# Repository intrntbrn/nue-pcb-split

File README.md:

# nue-pcb-split

- removed ansi bottom row (6.25u)
- removed iso support (split leftshift and iso enter)
- added 10u stabilizer holes
- added 1-2.75-2.25-1 split space option
- not tested! please select "confirm parts placement" when ordering from jlcpcb
  (this is due to jst connector shortage).

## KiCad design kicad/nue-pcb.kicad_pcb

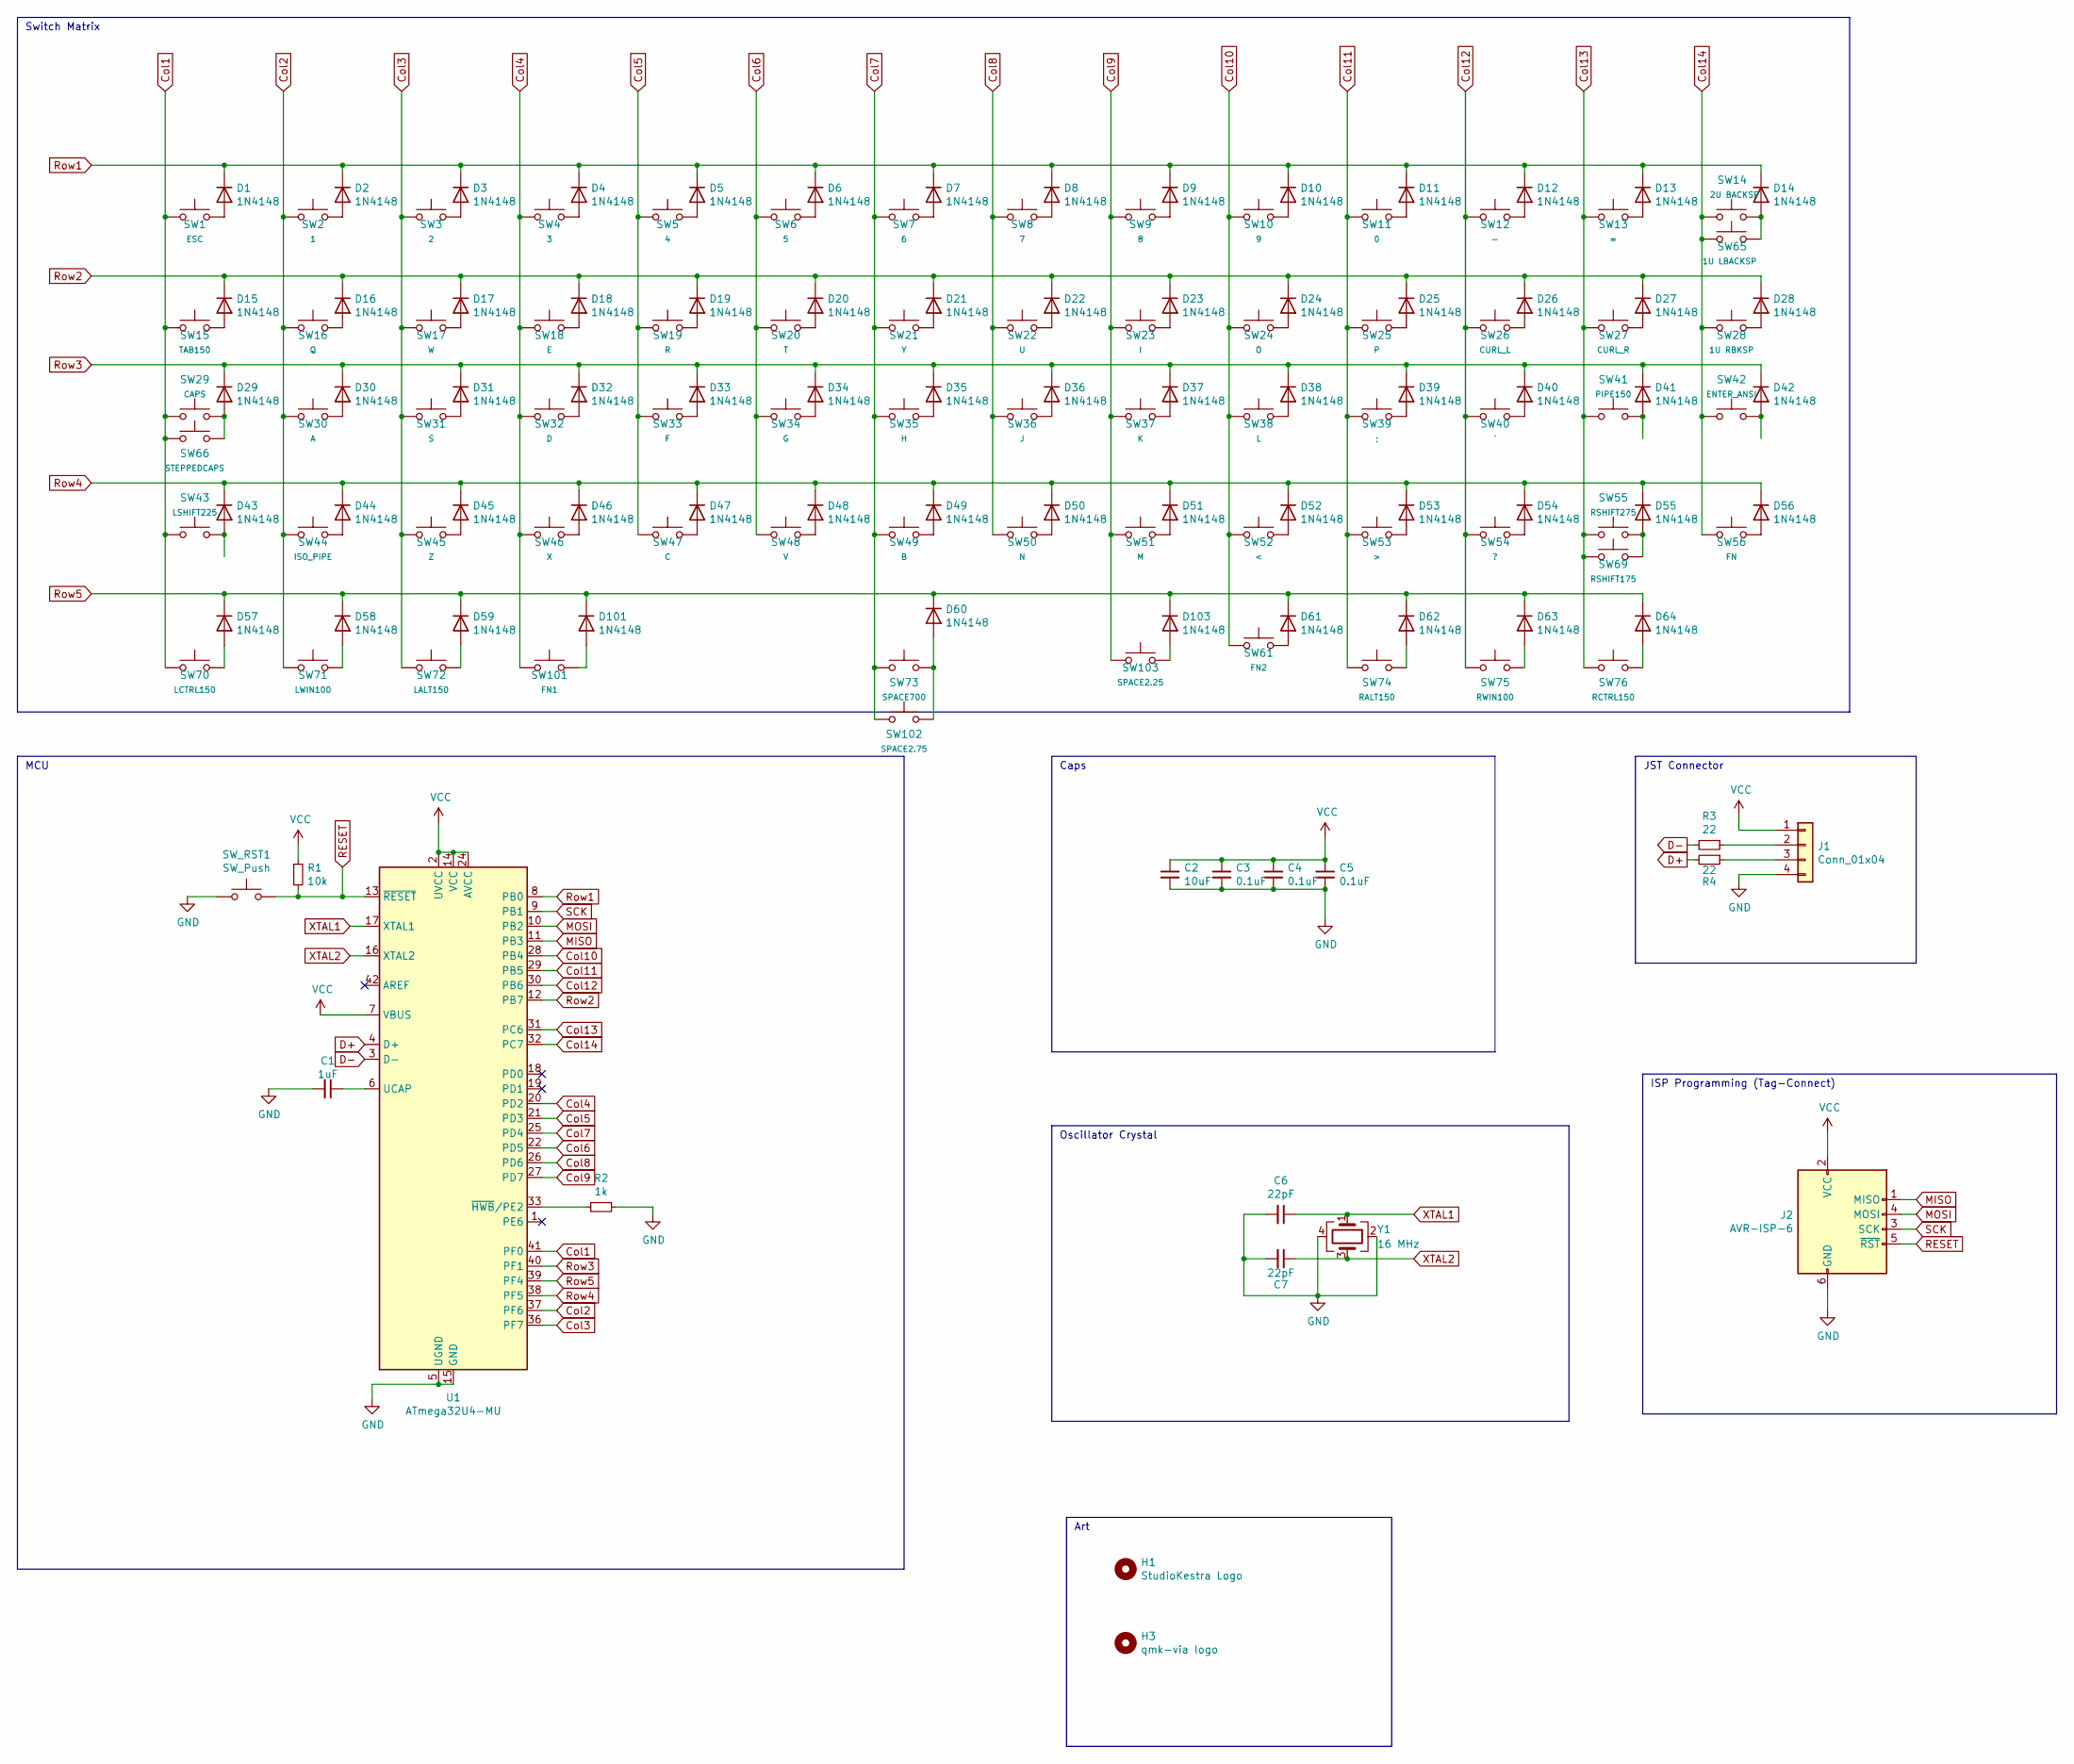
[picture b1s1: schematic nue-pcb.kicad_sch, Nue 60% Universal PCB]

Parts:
C1: 1uF; C_0603_1608Metric
C2: 10uF; C_0603_1608Metric
C3, C4, C5: 0.1uF; C_0603_1608Metric
C6, C7: 22pF; C_0603_1608Metric
D1, D2, D3, D4, D5, D6, D7, D8, D9, D10, D11, D12, D13, D14, D15, D16, D17, D18, D19, D20, D21, D22, D23, D24, D25, D26, D27, D28, D29, D30, D31, D32, D33, D34, D35, D36, D37, D38, D39, D40, D41, D42, D43, D44, D45, D46, D47, D48, D49, D50, D51, D52, D53, D54, D55, D56, D57, D58, D59, D60, D61, D62, D63, D64, D101, D103: 1N4148; D_SOD-123
H1: StudioKestra Logo; sk-square-mask-md
H3: qmk-via logo; qmk-via
J1: Conn_01x04; JST_BM04B-ASRS
J2: AVR-ISP-6; Conn_AVR_ISP_6
R1: 10k; R_0603_1608Metric
R2: 1k; R_0603_1608Metric
R3, R4: 22; R_0603_1608Metric
SW1: ESC; MX100
SW2: 1; MX100
SW3: 2; MX100
SW4: 3; MX100
SW5: 4; MX100
SW6: 5; MX100
SW7: 6; MX100
SW8: 7; MX100
SW9: 8; MX100
SW10: 9; MX100
SW11: 0; MX100
SW12: -; MX100
SW13: =; MX100
SW14: 2U BACKSP; MX200
SW15: TAB150; MX150
SW16: Q; MX100
SW17: W; MX100
SW18: E; MX100
SW19: R; MX100
SW20: T; MX100
SW21: Y; MX100
SW22: U; MX100
SW23: I; MX100
SW24: O; MX100
SW25: P; MX100
SW26: CURL_L; MX100
SW27: CURL_R; MX100
SW28: 1U RBKSP; MX100
SW29: CAPS; MX175
SW30: A; MX100
SW31: S; MX100
SW32: D; MX100
SW33: F; MX100
SW34: G; MX100
SW35: H; MX100
SW36: J; MX100
SW37: K; MX100
SW38: L; MX100
SW39: ;; MX100
SW40: '; MX100
SW41: PIPE150; MX150
SW42: ENTER_ANSI; MX225R
SW43: LSHIFT225; MX225
SW44: ISO_PIPE; MX100
SW45: Z; MX100
SW46: X; MX100
SW47: C; MX100
SW48: V; MX100
SW49: B; MX100
SW50: N; MX100
SW51: M; MX100
SW52: <; MX100
SW53: >; MX100
SW54: ?; MX100
SW55: RSHIFT275; MX275
SW56: FN; MX100
SW61: FN2; MX100
SW65: 1U LBACKSP; MX100
SW66: STEPPEDCAPS; MX125
SW69: RSHIFT175; MX175
SW70: LCTRL150; MX150
SW71: LWIN100; MX100
SW72: LALT150; MX150
SW73: SPACE700; MX10-7U
SW74: RALT150; MX150
SW75: RWIN100; MX100
SW76: RCTRL150; MX150
SW101: FN1; MX100
SW102: SPACE2.75; MX275R
SW103: SPACE2.25; MX225R
SW_RST1: SW_Push; pushbtn_C319436
U1: ATmega32U4-MU; QFN-44-1EP_7x7mm_P0.5mm_EP5.2x5.2mm
Y1: 16 MHz; Crystal_SMD_2520-4Pin_2.5x2.0mm

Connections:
Col1: SW1.1, SW15.1, SW29.1, SW43.1, SW66.1, SW70.1, U1.41 (PF0)
Col2: SW2.1, SW16.1, SW30.1, SW44.1, SW71.1, U1.37 (PF6)
Col3: SW3.1, SW17.1, SW31.1, SW45.1, SW72.1, U1.36 (PF7)
Col4: SW4.1, SW18.1, SW32.1, SW46.1, SW101.1, U1.20 (PD2)
Col5: SW5.1, SW19.1, SW33.1, SW47.1, U1.21 (PD3)
Col6: SW6.1, SW20.1, SW34.1, SW48.1, U1.22 (PD5)
Col7: SW7.1, SW21.1, SW35.1, SW49.1, SW73.2, SW102.2, U1.25 (PD4)
Col8: SW8.1, SW22.1, SW36.1, SW50.1, U1.26 (PD6)
Col9: SW9.1, SW23.1, SW37.1, SW51.1, SW103.1, U1.27 (PD7)
Col10: SW10.1, SW24.1, SW38.1, SW52.1, SW61.1, U1.28 (PB4)
Col11: SW11.1, SW25.1, SW39.1, SW53.1, SW74.1, U1.29 (PB5)
Col12: SW12.1, SW26.1, SW40.1, SW54.1, SW75.1, U1.30 (PB6)
Col13: SW13.1, SW27.1, SW41.1, SW55.1, SW69.1, SW76.1, U1.31 (PC6)
Col14: SW14.1, SW28.1, SW42.1, SW56.1, SW65.1, U1.32 (PC7)
D+: R4.2, U1.4 (D+)
D-: R3.2, U1.3 (D-)
GND: C1.2, C2.2, C3.2, C4.2, C5.2, C6.2, C7.2, J1.4, J2.6 (GND), R2.1, SW_RST1.1, U1.5 (UGND), U1.15 (GND), U1.23 (GND), U1.35 (GND), U1.43 (GND), U1.45 (GND), Y1.2, Y1.4
MISO: J2.1 (MISO), U1.11 (PB3)
MOSI: J2.4 (MOSI), U1.10 (PB2)
unnamed: C1.1, U1.6 (UCAP)
unnamed: D1.2 (A), SW1.2
unnamed: D2.2 (A), SW2.2
unnamed: D3.2 (A), SW3.2
unnamed: D4.2 (A), SW4.2
unnamed: D5.2 (A), SW5.2
unnamed: D6.2 (A), SW6.2
unnamed: D7.2 (A), SW7.2
unnamed: D8.2 (A), SW8.2
unnamed: D9.2 (A), SW9.2
unnamed: D10.2 (A), SW10.2
unnamed: D11.2 (A), SW11.2
unnamed: D12.2 (A), SW12.2
unnamed: D13.2 (A), SW13.2
unnamed: D14.2 (A), SW14.2, SW65.2
unnamed: D15.2 (A), SW15.2
unnamed: D16.2 (A), SW16.2
unnamed: D17.2 (A), SW17.2
unnamed: D18.2 (A), SW18.2
unnamed: D19.2 (A), SW19.2
unnamed: D20.2 (A), SW20.2
unnamed: D21.2 (A), SW21.2
unnamed: D22.2 (A), SW22.2
unnamed: D23.2 (A), SW23.2
unnamed: D24.2 (A), SW24.2
unnamed: D25.2 (A), SW25.2
unnamed: D26.2 (A), SW26.2
unnamed: D27.2 (A), SW27.2
unnamed: D28.2 (A), SW28.2
unnamed: D29.2 (A), SW29.2, SW66.2
unnamed: D30.2 (A), SW30.2
unnamed: D31.2 (A), SW31.2
unnamed: D32.2 (A), SW32.2
unnamed: D33.2 (A), SW33.2
unnamed: D34.2 (A), SW34.2
unnamed: D35.2 (A), SW35.2
unnamed: D36.2 (A), SW36.2
unnamed: D37.2 (A), SW37.2
unnamed: D38.2 (A), SW38.2
unnamed: D39.2 (A), SW39.2
unnamed: D40.2 (A), SW40.2
unnamed: D41.2 (A), SW41.2
unnamed: D42.2 (A), SW42.2
unnamed: D43.2 (A), SW43.2
unnamed: D44.2 (A), SW44.2
unnamed: D45.2 (A), SW45.2
unnamed: D46.2 (A), SW46.2
unnamed: D47.2 (A), SW47.2
unnamed: D48.2 (A), SW48.2
unnamed: D49.2 (A), SW49.2
unnamed: D50.2 (A), SW50.2
unnamed: D51.2 (A), SW51.2
unnamed: D52.2 (A), SW52.2
unnamed: D53.2 (A), SW53.2
unnamed: D54.2 (A), SW54.2
unnamed: D55.2 (A), SW55.2, SW69.2
unnamed: D56.2 (A), SW56.2
unnamed: D57.2 (A), SW70.2
unnamed: D58.2 (A), SW71.2
unnamed: D59.2 (A), SW72.2
unnamed: D60.2 (A), SW73.1, SW102.1
unnamed: D61.2 (A), SW61.2
unnamed: D62.2 (A), SW74.2
unnamed: D63.2 (A), SW75.2
unnamed: D64.2 (A), SW76.2
unnamed: D101.2 (A), SW101.2
unnamed: D103.2 (A), SW103.2
unnamed: J1.2, R3.1
unnamed: J1.3, R4.1
unnamed: R2.2, U1.33 (~HWB/PE2)
RESET: J2.5 (~RST), R1.2, SW_RST1.2, U1.13 (~RESET)
Row1: D1.1 (K), D2.1 (K), D3.1 (K), D4.1 (K), D5.1 (K), D6.1 (K), D7.1 (K), D8.1 (K), D9.1 (K), D10.1 (K), D11.1 (K), D12.1 (K), D13.1 (K), D14.1 (K), U1.8 (PB0)
Row2: D15.1 (K), D16.1 (K), D17.1 (K), D18.1 (K), D19.1 (K), D20.1 (K), D21.1 (K), D22.1 (K), D23.1 (K), D24.1 (K), D25.1 (K), D26.1 (K), D27.1 (K), D28.1 (K), U1.12 (PB7)
Row3: D29.1 (K), D30.1 (K), D31.1 (K), D32.1 (K), D33.1 (K), D34.1 (K), D35.1 (K), D36.1 (K), D37.1 (K), D38.1 (K), D39.1 (K), D40.1 (K), D41.1 (K), D42.1 (K), U1.40 (PF1)
Row4: D43.1 (K), D44.1 (K), D45.1 (K), D46.1 (K), D47.1 (K), D48.1 (K), D49.1 (K), D50.1 (K), D51.1 (K), D52.1 (K), D53.1 (K), D54.1 (K), D55.1 (K), D56.1 (K), U1.38 (PF5)
Row5: D57.1 (K), D58.1 (K), D59.1 (K), D60.1 (K), D61.1 (K), D62.1 (K), D63.1 (K), D64.1 (K), D101.1 (K), D103.1 (K), U1.39 (PF4)
SCK: J2.3 (SCK), U1.9 (PB1)
VCC: C2.1, C3.1, C4.1, C5.1, J1.1, J2.2 (VCC), R1.1, U1.2 (UVCC), U1.7 (VBUS), U1.14 (VCC), U1.24 (AVCC), U1.34 (VCC), U1.44 (AVCC)
XTAL1: C6.1, U1.17 (XTAL1), Y1.1
XTAL2: C7.1, U1.16 (XTAL2), Y1.3

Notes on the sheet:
Oscillator Crystal
MCU
ISP Programming (Tag-Connect)
JST Connector
Caps
Switch Matrix
Art

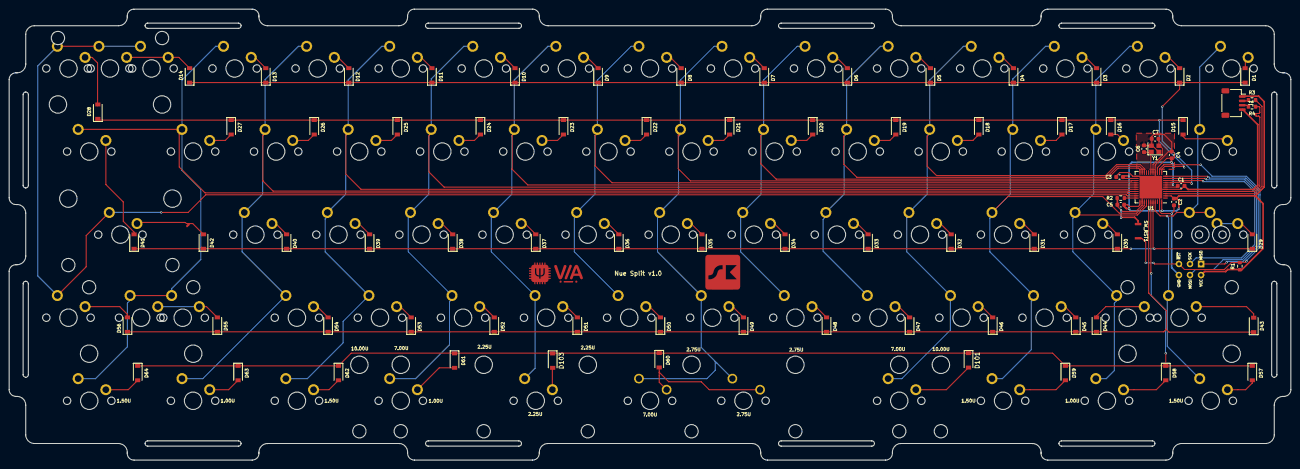
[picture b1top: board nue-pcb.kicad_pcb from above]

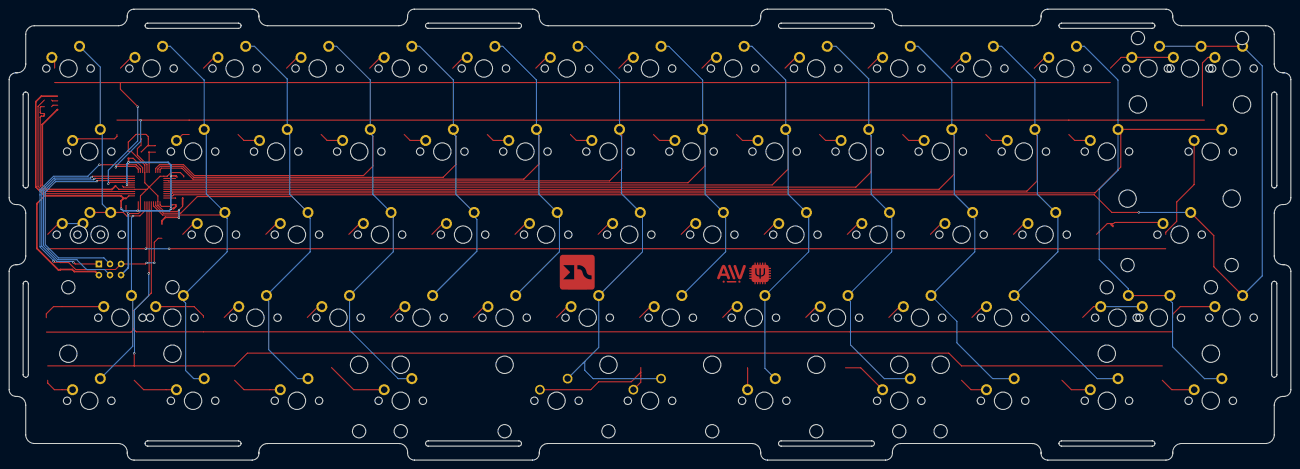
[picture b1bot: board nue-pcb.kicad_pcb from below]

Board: 2 copper layers, 293.9 x 103.4 mm, 154 parts (2 on the bottom side), 99 nets.

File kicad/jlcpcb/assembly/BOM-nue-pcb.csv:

Comment,Designator,Footprint,LCSC
Conn_01x04,J1,JST_SH_SM04B-SRSS-TB_1x04-1MP_P1.00mm_Horizontal,C145956
0.1uF,"C3,C4,C5",C_0603_1608Metric,C14663
1uF,C1,C_0603_1608Metric,C15849
22pF,"C6,C7",C_0603_1608Metric,C1653
10uF,C2,C_0603_1608Metric,C19702
1k,R2,R_0603_1608Metric,C21190
22,"R3,R4",R_0603_1608Metric,C23345
10k,R1,R_0603_1608Metric,C25804
16 MHz,Y1,Crystal_SMD_2520-4Pin_2.5x2.0mm,C284159
SW_Push,SW_RST1,pushbtn_C319436,C319436
ATmega32U4-MU,U1,QFN-44-1EP_7x7mm_P0.5mm_EP5.2x5.2mm,C45874
1N4148,"D1,D10,D101,D103,D11,D12,D13,D14,D15,D16,D17,D18,D19,D2,D20,D21,D22,D23,D24,D25,D26,D27,D28,D29,D3,D30,D31,D32,D33,D34,D35,D36,D37,D38,D39,D4,D40,D41,D42,D43,D44,D45,D46,D47,D48,D49,D5,D50,D51,D52,D53,D54,D55,D56,D57,D58,D59,D6,D60,D61,D62,D63,D64,D7,D8,D9",D_SOD-123,C81598
ESC,SW1,MX100,
1,SW2,MX100,
2,SW3,MX100,
3,SW4,MX100,
4,SW5,MX100,
5,SW6,MX100,
6,SW7,MX100,
7,SW8,MX100,
8,SW9,MX100,
9,SW10,MX100,
0,SW11,MX100,
-,SW12,MX100,
=,SW13,MX100,
2U BACKSP,SW14,MX200,
Q,SW16,MX100,
W,SW17,MX100,
E,SW18,MX100,
R,SW19,MX100,
T,SW20,MX100,
Y,SW21,MX100,
U,SW22,MX100,
I,SW23,MX100,
O,SW24,MX100,
P,SW25,MX100,
CURL_L,SW26,MX100,
CURL_R,SW27,MX100,
1U RBKSP,SW28,MX100,
S,SW31,MX100,
D,SW32,MX100,
F,SW33,MX100,
G,SW34,MX100,
J,SW36,MX100,
K,SW37,MX100,
L,SW38,MX100,
;,SW39,MX100,
',SW40,MX100,
PIPE150,SW41,MX150,
LSHIFT225,SW43,MX225,
Z,SW45,MX100,
X,SW46,MX100,
B,SW49,MX100,
N,SW50,MX100,
M,SW51,MX100,
?,SW54,MX100,
RSHIFT275,SW55,MX275,
FN,SW56,MX100,
FN2,SW61,MX100,
1U LBACKSP,SW65,MX100,
RSHIFT175,SW69,MX175,
LCTRL150,SW70,MX150,
LWIN100,SW71,MX100,
RALT150,SW74,MX150,
RWIN100,SW75,MX100,
RCTRL150,SW76,MX150,
ISO_PIPE,SW44,MX100,
SPACE700,SW73,MX10-7U,
V,SW48,MX100,
C,SW47,MX100,
ENTER_ANSI,SW42,MX225R,
CAPS,SW29,MX175,
TAB150,SW15,MX150,
STEPPEDCAPS,SW66,MX125,
H,SW35,MX100,
A,SW30,MX100,
LALT150,SW72,MX150,
SPACE2.25,SW103,MX225R,
SPACE2.75,SW102,MX275R,
FN1,SW101,MX100,

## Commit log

2022-08-07 fix typo
    fix typo
2022-08-08 jlcpcb order hint
2022-08-19 replace jst footprint, make 2.75/7/10u holes smaller
2022-08-19 provide vial json
2022-08-19 add more vial options
